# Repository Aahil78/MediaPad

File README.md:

# MediaPad

MediaPad is an open-source, 3x4 macropad. It's powered by the Seeed Studio XIAO nRF52840 but can also be used with a Seeed Studio XIAO RP2040.

## Features:
  - 12 Hotswappable MX Switches
  - EC11 Rotary Encoder
  - Seeed Studio XIAO RP2040/nRF52840
  - (Optionable) Battery Support (Built in BMS on MCU)
  - ARGB Backlighting (SK6812-E)
  - Diodes to provide anti-ghosting
  - 3D Printed enclosure

## Images

### Schematic:

### PCB:

### Case:

### Full assembly:

## BOM:

| Designator                                                                 | Quantity | Value                   | Footprint                                         | Package | MPN | DNP | Mount_Type | Description                                                                        | PROD_ID   | Voltage | Tolerance | Sim.Device | Sim.Pins |
|----------------------------------------------------------------------------|----------|-------------------------|---------------------------------------------------|---------|-----|-----|------------|------------------------------------------------------------------------------------|-----------|---------|-----------|------------|----------|
| C1, C14                                                                    | 2        | 10uF                    | C_0402_1005Metric                                 |         |     |     | smt        | Unpolarized capacitor                                                              | CAP-14848 | 6.3V    | 20%       |            |          |
| C10, C11, C12, C13, C2, C3, C4, C5, C6, C7, C8, C9                         | 12       | 0.1uF                   | C_0402_1005Metric                                 |         |     |     | smt        | Unpolarized capacitor                                                              | CAP-25565 | 16V     | 10%       |            |          |
| D10, D11, D12, D13, D2, D3, D4, D5, D6, D7, D8, D9                         | 12       | D                       | D_0402_1005Metric                                 |         |     |     | smt        | Diode                                                                              |           |         |           | D          | 1=K 2=A  |
| LED10, LED11, LED12, LED13, LED2, LED3, LED4, LED5, LED6, LED7, LED8, LED9 | 12       | SK6812                  | MX_SK6812MINI-E                                   |         |     |     | tht        | RGB LED with integrated controller                                                 |           |         |           |            |          |
| R1                                                                         | 1        | 330ohm                  | R_Axial_DIN0207_L6.3mm_D2.5mm_P10.16mm_Horizontal |         |     |     | tht        | 330Ω, 1/4W Resistor                                                                |           |         |           |            |          |
| SW1                                                                        | 1        | RotaryEncoder_Switch_MP | RotaryEncoder_Alps_EC11E-Switch_Vertical_H20mm    |         |     |     | tht        | Rotary encoder, dual channel, incremental quadrate outputs, with switch and MP Pin |           |         |           |            |          |
| SW10, SW11, SW12, SW13, SW2, SW3, SW4, SW5, SW6, SW7, SW8, SW9             | 12       | SW_Push                 | SW_Hotswap_Kailh_Choc_V1                          |         |     |     | smt        | Push button switch, generic, two pins                                              |           |         |           |            |          |
| U1                                                                         | 1        | XIAO-nRF52840-DIP       | XIAO-nRF52840-DIP                                 |         |     |     | smt        |                                                                                    |           |         |           |            |          |
| U2                                                                         | 1        | SN74AHCT125DR           | SOIC127P600X175-14N                               |         |     |     | smt        |                                                                                    |           |         |           |            |          |

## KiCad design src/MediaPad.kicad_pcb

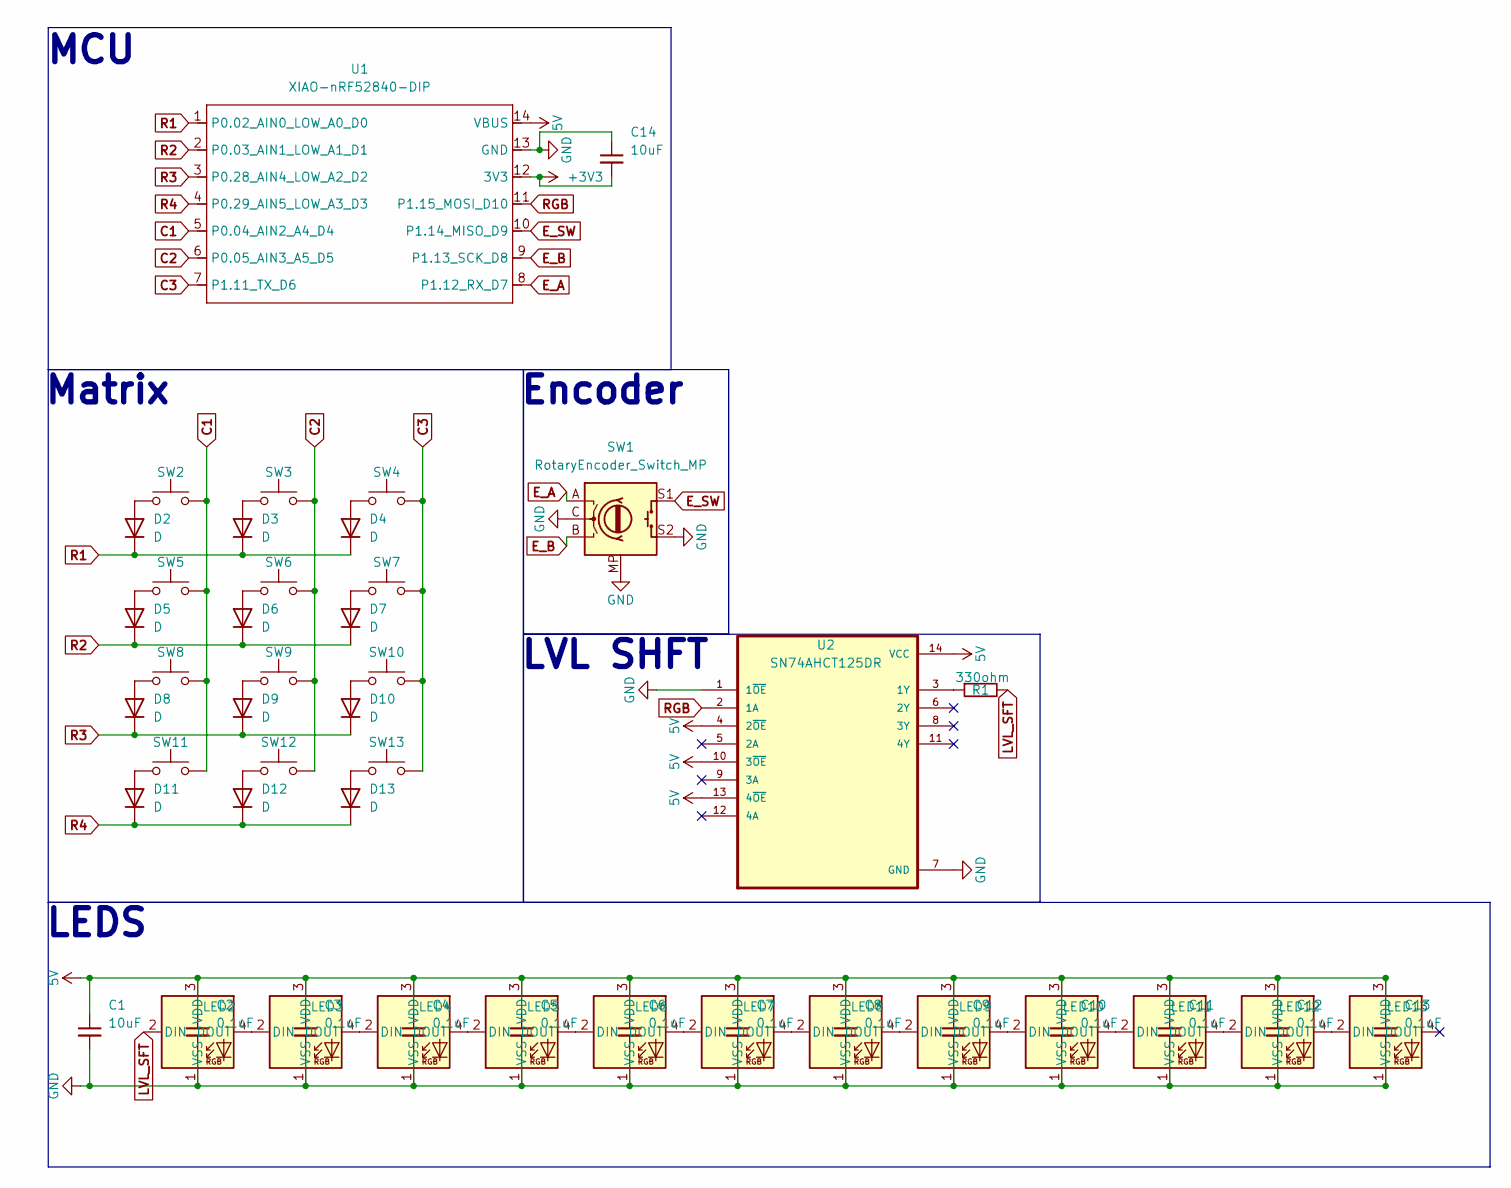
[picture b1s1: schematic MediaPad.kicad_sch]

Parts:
C1, C14: 10uF; C_0402_1005Metric; Voltage 6.3V; Tolerance 20%
C2, C3, C4, C5, C6, C7, C8, C9, C10, C11, C12, C13: 0.1uF; C_0402_1005Metric; Voltage 16V; Tolerance 10%
D2, D3, D4, D5, D6, D7, D8, D9, D10, D11, D12, D13: D; D_0402_1005Metric
LED2, LED3, LED4, LED5, LED6, LED7, LED8, LED9, LED10, LED11, LED12, LED13: SK6812; MX_SK6812MINI-E
R1: 330ohm; R_Axial_DIN0207_L6.3mm_D2.5mm_P10.16mm_Horizontal
SW1: RotaryEncoder_Switch_MP; RotaryEncoder_Alps_EC11E-Switch_Vertical_H20mm
SW2, SW3, SW4, SW5, SW6, SW7, SW8, SW9, SW10, SW11, SW12, SW13: SW_Push; SW_Hotswap_Kailh_Choc_V1
U1: XIAO-nRF52840-DIP
U2: SN74AHCT125DR; SOIC127P600X175-14N

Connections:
5V: C1.1, C2.1, C3.1, C4.1, C5.1, C6.1, C7.1, C8.1, C9.1, C10.1, C11.1, C12.1, C13.1, LED2.3 (VDD), LED3.3 (VDD), LED4.3 (VDD), LED5.3 (VDD), LED6.3 (VDD), LED7.3 (VDD), LED8.3 (VDD), LED9.3 (VDD), LED10.3 (VDD), LED11.3 (VDD), LED12.3 (VDD), LED13.3 (VDD), U1.14 (VBUS), U2.4 (2~OE), U2.10 (3~OE), U2.13 (4~OE), U2.14 (VCC)
+3V3: C14.2, U1.12 (3V3)
C1: SW2.2, SW5.2, SW8.2, SW11.2, U1.5 (P0.04_AIN2_A4_D4)
C2: SW3.2, SW6.2, SW9.2, SW12.2, U1.6 (P0.05_AIN3_A5_D5)
C3: SW4.2, SW7.2, SW10.2, SW13.2, U1.7 (P1.11_TX_D6)
E_A: SW1.A, U1.8 (P1.12_RX_D7)
E_B: SW1.B, U1.9 (P1.13_SCK_D8)
E_SW: SW1.S1, U1.10 (P1.14_MISO_D9)
GND: C1.2, C2.2, C3.2, C4.2, C5.2, C6.2, C7.2, C8.2, C9.2, C10.2, C11.2, C12.2, C13.2, C14.1, LED2.1 (VSS), LED3.1 (VSS), LED4.1 (VSS), LED5.1 (VSS), LED6.1 (VSS), LED7.1 (VSS), LED8.1 (VSS), LED9.1 (VSS), LED10.1 (VSS), LED11.1 (VSS), LED12.1 (VSS), LED13.1 (VSS), SW1.C, SW1.MP, SW1.S2, U1.13 (GND), U2.1 (1~OE), U2.7 (GND)
LVL_SFT: LED2.2 (DIN), R1.2
unnamed: D2.2 (A), SW2.1
unnamed: D3.2 (A), SW3.1
unnamed: D4.2 (A), SW4.1
unnamed: D5.2 (A), SW5.1
unnamed: D6.2 (A), SW6.1
unnamed: D7.2 (A), SW7.1
unnamed: D8.2 (A), SW8.1
unnamed: D9.2 (A), SW9.1
unnamed: D10.2 (A), SW10.1
unnamed: D11.2 (A), SW11.1
unnamed: D12.2 (A), SW12.1
unnamed: D13.2 (A), SW13.1
unnamed: LED2.4 (DOUT), LED3.2 (DIN)
unnamed: LED3.4 (DOUT), LED4.2 (DIN)
unnamed: LED4.4 (DOUT), LED5.2 (DIN)
unnamed: LED5.4 (DOUT), LED6.2 (DIN)
unnamed: LED6.4 (DOUT), LED7.2 (DIN)
unnamed: LED7.4 (DOUT), LED8.2 (DIN)
unnamed: LED8.4 (DOUT), LED9.2 (DIN)
unnamed: LED9.4 (DOUT), LED10.2 (DIN)
unnamed: LED10.4 (DOUT), LED11.2 (DIN)
unnamed: LED11.4 (DOUT), LED12.2 (DIN)
unnamed: LED12.4 (DOUT), LED13.2 (DIN)
unnamed: R1.1, U2.3 (1Y)
R1: D2.1 (K), D3.1 (K), D4.1 (K), U1.1 (P0.02_AIN0_LOW_A0_D0)
R2: D5.1 (K), D6.1 (K), D7.1 (K), U1.2 (P0.03_AIN1_LOW_A1_D1)
R3: D8.1 (K), D9.1 (K), D10.1 (K), U1.3 (P0.28_AIN4_LOW_A2_D2)
R4: D11.1 (K), D12.1 (K), D13.1 (K), U1.4 (P0.29_AIN5_LOW_A3_D3)
RGB: U1.11 (P1.15_MOSI_D10), U2.2 (1A)

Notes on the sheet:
Encoder
LEDS
MCU
LVL SHFT
Matrix

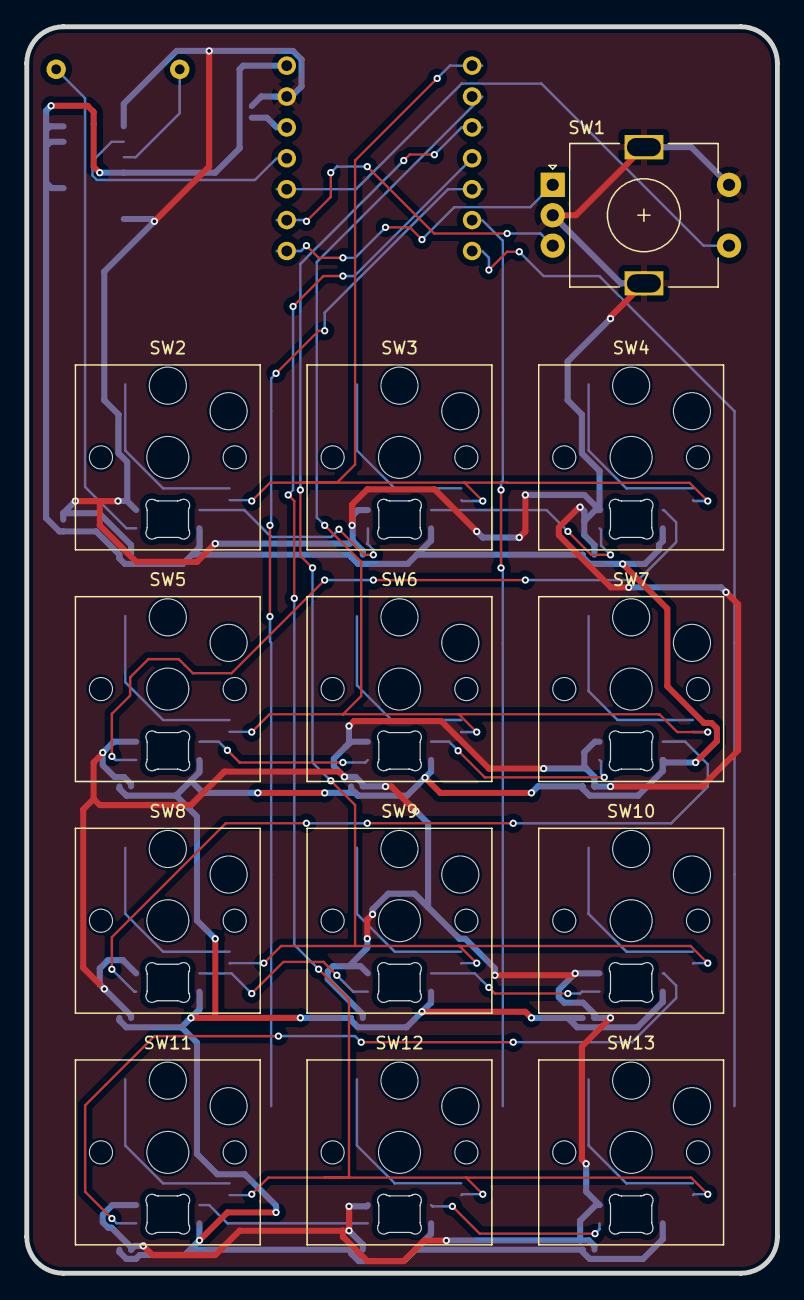
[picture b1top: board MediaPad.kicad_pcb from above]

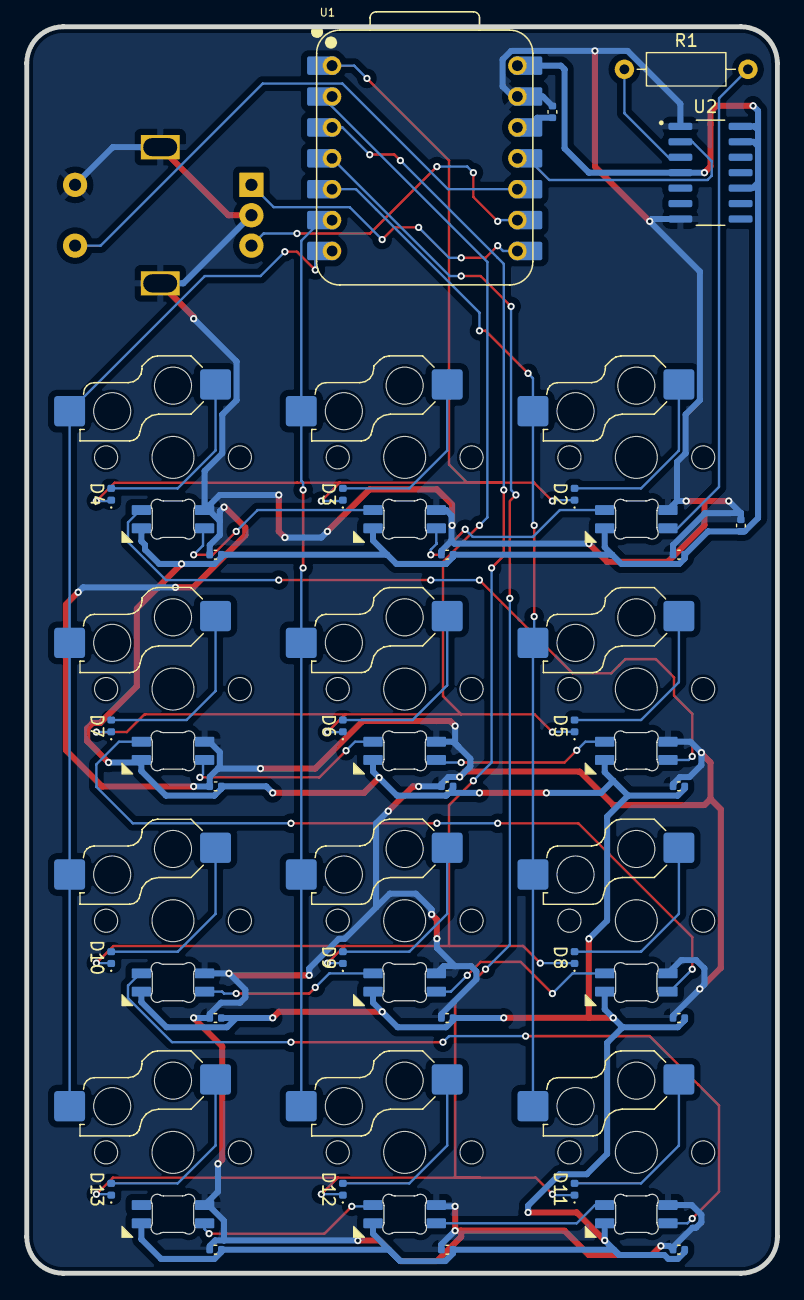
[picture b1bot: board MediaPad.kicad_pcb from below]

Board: 2 copper layers, 61.7 x 102.5 mm, 54 parts (29 on the bottom side), 39 nets.

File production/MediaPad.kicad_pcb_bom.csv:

Designator,Quantity,Value,Footprint,Package,MPN,DNP,Mount_Type,Description,PROD_ID,Voltage,Tolerance,Sim.Device,Sim.Pins
"C1, C14",2,10uF,C_0402_1005Metric,,,,smt,Unpolarized capacitor,CAP-14848,6.3V,20%,,
"C10, C11, C12, C13, C2, C3, C4, C5, C6, C7, C8, C9",12,0.1uF,C_0402_1005Metric,,,,smt,Unpolarized capacitor,CAP-25565,16V,10%,,
"D10, D11, D12, D13, D2, D3, D4, D5, D6, D7, D8, D9",12,D,D_0402_1005Metric,,,,smt,Diode,,,,D,1=K 2=A
"LED10, LED11, LED12, LED13, LED2, LED3, LED4, LED5, LED6, LED7, LED8, LED9",12,SK6812,MX_SK6812MINI-E,,,,tht,RGB LED with integrated controller,,,,,
R1,1,330ohm,R_Axial_DIN0207_L6.3mm_D2.5mm_P10.16mm_Horizontal,,,,tht,"330Ω, 1/4W Resistor",,,,,
SW1,1,RotaryEncoder_Switch_MP,RotaryEncoder_Alps_EC11E-Switch_Vertical_H20mm,,,,tht,"Rotary encoder, dual channel, incremental quadrate outputs, with switch and MP Pin",,,,,
"SW10, SW11, SW12, SW13, SW2, SW3, SW4, SW5, SW6, SW7, SW8, SW9",12,SW_Push,SW_Hotswap_Kailh_Choc_V1,,,,smt,"Push button switch, generic, two pins",,,,,
U1,1,XIAO-nRF52840-DIP,XIAO-nRF52840-DIP,,,,smt,,,,,,
U2,1,SN74AHCT125DR,SOIC127P600X175-14N,,,,smt,,,,,,

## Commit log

2026-03-02 Create temp
2026-03-02 Enhance README with product details and BOM
    Expanded README with detailed product description, features, images, and BOM.
